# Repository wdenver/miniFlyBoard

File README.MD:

# mini fly board

Esta placa deve ser compatível com o naze32.
Projetada para ser simples e pequena. Para ser usada com receptores convencionais.

Possui um monitor da tensão da bateria e um mosfet para acionamento genérico.
Pode ser montada utilizando as mini placas mpu6050.

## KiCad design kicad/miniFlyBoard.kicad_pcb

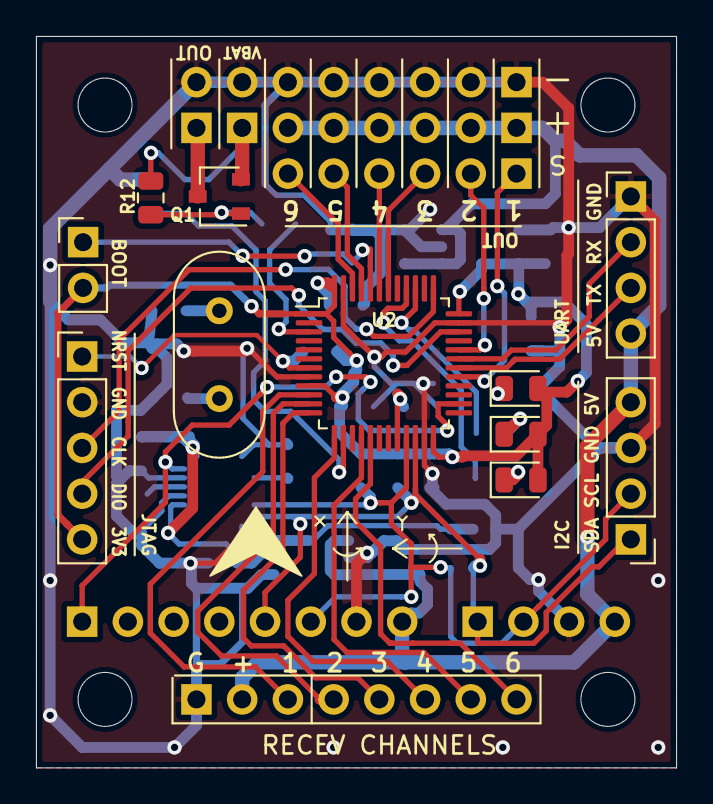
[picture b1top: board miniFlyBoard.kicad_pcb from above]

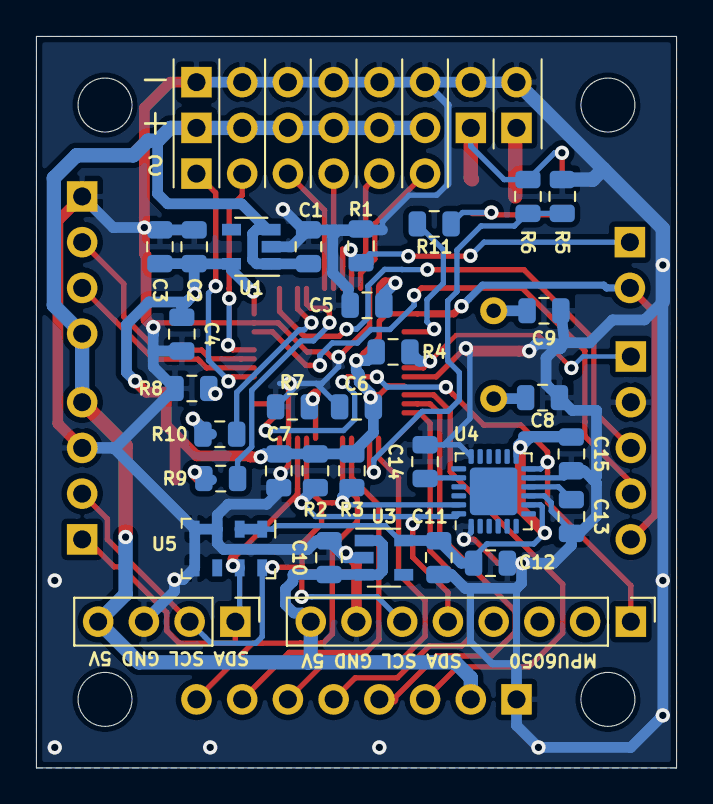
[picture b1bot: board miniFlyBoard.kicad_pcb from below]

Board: 2 copper layers, 35.6 x 40.6 mm, 53 parts (32 on the bottom side), 40 nets.

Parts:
C1, C2, C10, C11: 1uf; C_0805_2012Metric
C3, C12: 10uf; C_0805_2012Metric
C4, C5, C6, C7, C13, C14, C15: 100nf; C_0805_2012Metric
C8, C9: C; C_0805_2012Metric
D1, D2, D3: LED; LED_0805_2012Metric
H1, H2, H3, H4: MountingHole; MountingHole_3mm
J1: MPU6050; PinHeader_1x08_P2.54mm_Vertical
J2: Conn_01x04_Female; PinHeader_1x04_P2.54mm_Vertical
J3: VBAT; PinHeader_1x02_P2.54mm_Vertical
J4: BOOT; PinHeader_1x02_P2.54mm_Vertical
J5: RECEV CHANNELS; PinHeader_1x08_P2.54mm_Vertical
J6, J7, J8: ESC OUT; PinHeader_1x06_P2.54mm_Vertical
J9: UART; PinHeader_1x04_P2.54mm_Vertical
J10: I2C; PinHeader_1x04_P2.54mm_Vertical
J11: JTAG; PinHeader_1x05_P2.54mm_Vertical
J12: out; PinHeader_1x02_P2.54mm_Vertical
Q1: Q_PMOS_GSD; SOT-23W
R1, R4, R5, R7, R11, R12: 10k; R_0805_2012Metric
R2, R3: 4.7k; R_0805_2012Metric
R6: 1K; R_0805_2012Metric
R8, R9, R10: 100; R_0805_2012Metric
U1, U3: MIC5504-3.3YM5; SOT-23-5
U2: STM32F103C8Tx; LQFP-48_7x7mm_P0.5mm
U4: MPU-6050_NRND; QFN-24-1EP_4x4mm_P0.5mm_EP2.65x2.65mm
U5: MS5611-01BA; LGA-8_3x5mm_P1.25mm
Y1: Crystal; Crystal_HC49-4H_Vertical

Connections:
+3V3: C2.1, C3.1, C4.1, C5.1, C6.1, C7.1, D1.2, D2.2, D3.2, J4.2, J11.5, R2.1, R3.1, R4.1, U1.5, U2.1, U2.9, U2.24, U2.36, U2.48
+5V: C1.1, C10.1, J1.8, J2.4, J5.2, J8.1, J8.2, J8.3, J8.4, J8.5, J8.6, J9.4, J10.4, U1.1, U1.3, U3.1, U3.3
/BOOT0: J4.1, R1.1, U2.44
/BOOT1: R7.1, U2.20
/LED0: R9.2, U2.40
/LED1: R10.2, U2.39
/MPU_INT: J1.1, U2.26, U4.12
/NRST: J11.1, R4.2, U2.7
/POWER_ADC: R5.2, R6.1, U2.14
/POWER_EN: R11.1, U2.3
/PWM1: J6.1, U2.29
/PWM2: J6.2, U2.32
/PWM3: J6.3, U2.42
/PWM4: J6.4, U2.43
/PWM5: J6.5, U2.45
/PWM6: J6.6, U2.46
/RC_CH1: J5.3, U2.10
/RC_CH2: J5.4, U2.11
/RC_CH3: J5.5, U2.12
/RC_CH4: J5.6, U2.13
/RC_CH5: J5.7, U2.16
/RC_CH6: J5.8, U2.17
/RX0: J9.2, U2.31
/SCL: J1.6, J2.2, J10.2, R3.2, U2.21, U4.23, U5.8
/SDA: J1.5, J2.1, J10.1, R2.2, U2.22, U4.24, U5.7
/SWDCLK: J11.3, U2.37
/SWDIO: J11.4, U2.34
/TX0: J9.3, U2.30
/osc1: C9.1, Y1.2
/osc2: C8.1, Y1.1
/vbat: J3.1, Q1.2, R6.2, R12.1
GND: C1.2, C2.2, C3.2, C4.2, C5.2, C6.2, C7.2, C8.2, C9.2, C10.2, C11.2, C12.2, C13.2, C14.2, C15.2, J1.7, J2.3, J3.2, J5.1, J7.1, J7.2, J7.3, J7.4, J7.5, J7.6, J9.1, J10.3, J11.2, J12.2, R1.2, R5.1, R7.2, R8.2, U1.2, U2.8, U2.23, U2.35, U2.47, U3.2, U4.1, U4.9, U4.11, U4.18, U5.3, U5.4, U5.5
unnamed: C13.1, U4.10
unnamed: C14.1, U4.20
unnamed: D1.1, R8.1
unnamed: D2.1, R9.1
unnamed: D3.1, R10.1
unnamed: J12.1, Q1.3
unnamed: Q1.1, R11.2, R12.2
VSENS: C11.1, C12.1, C15.1, U3.5, U4.8, U4.13, U5.1, U5.2

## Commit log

2021-04-17 update back image
2021-04-19 adicionado gitignore
2021-04-19 mudanças na pcb
2021-04-19 removido arquivos desnecessários
2021-04-19 removido arquivo .net
